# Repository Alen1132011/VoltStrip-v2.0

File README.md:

# Voltstrip V2.0

A casual, open-source 4-key mechanical macropad featuring an OLED display, a rotary encoder, and clean RGB underglow. Powered by the Seeed Studio XIAO RP2040 and running on QMK/Vial firmware so you can remap everything on the fly without breaking a sweat.

Built and submitted as part of the Hack Club Stardance program.

---

## What's Under the Hood?

* **The Controller:** Seeed Studio XIAO RP2040—super compact, fast, and budget-friendly.
* **The Keys:** 4 mechanical switches (Cherry MX compatible), meaning you can swap in whatever linears, tactiles, or clickies you prefer.
* **The Dial:** 1x EC11 rotary encoder with a built-in push button, ideal for adjusting volume, scrolling timelines, or brush sizing.
* **The Screen:** A crisp 0.91" I2C OLED display (128x32 resolution) to show off active layers, custom graphics, or profile states.
* **The Glow:** 1x addressable WS2812B RGB LED tucked underneath to give your desk that perfect ambient underglow.
* **The Software:** Fully compatible with QMK and Vial for painless, real-time layout configurations.

---

## Design & Gallery

Here is the complete project breakdown, moving from the initial electrical routing up to the final 3D-printed enclosure.

Spin it in 3D!
>  **[CLICK HERE TO VIEW THE PCB IN YOUR BROWSER via KiCanvas](https://kicanvas.org/?repo=https%3A%2F%2Fgithub.com%2FAlen1132011%2FVoltStrip-v2.0%2Ftree%2Fmain%2FPCB)**

### Layout & Concept
The overall alignment of the keys, encoder, and display panel on the top plate.

### Schematic Diagram
A clean, straightforward schematic showing how all components route back to the XIAO's GPIO pins.

### PCB Layout
Double-sided PCB design with optimized traces, dedicated ground planes, and custom silkscreen art on the back.

### Enclosure & Fit
The custom-designed 3D-printed shell. Tolerances are dialed in to ensure a perfectly flush fit for both the top plate and bottom shell pieces.

---

## Bill of Materials (BOM)

| Component | Qty | Description | Notes |
| :--- | :---: | :--- | :--- |
| **Seeed Studio XIAO RP2040** | 1 | Microcontroller Board | SMT Module / Direct Solder |
| **Cherry MX Compatible Switches** | 4 | Mechanical Key Switches | 3-pin or 5-pin plate mount |
| **EC11 Rotary Encoder** | 1 | Navigation & Volume Control | Through-Hole (THT) with push button |
| **0.91" OLED Display** | 1 | 128x32 I2C Screen | Connects via 4-pin header |
| **1N4148 Diode** | 4 | Matrix Diodes | DO-35 THT or equivalent SMD |
| **WS2812B RGB LED** | 1 | Addressable Underglow LED | 5050 / PLCC-4 package |
| **Custom Case** | 1 | 3D Printed Top & Bottom Shell | PLA or PETG (printed at 0.20mm) |

---

## Hardware Configuration & Pin Map

If you're modifying the code or setting up your own layout config, here is exactly where everything plugs into the RP2040:

* **Rows:** `GP29` (D3), `GP28` (D2)
* **Columns:** `GP27` (D1), `GP26` (D0), `GP4` (D9)
* **Rotary Encoder:** `GP2` (D8), `GP1` (D7)
* **RGB Data:** `GP3` (D10)
* **I2C Display (OLED):** Standard RP2040 SDA & SCL pins

---

## License

This project is fully open-source. Feel free to grab the files, remix the layout, spin up your own PCBs, or tweak the shell to make it your own!

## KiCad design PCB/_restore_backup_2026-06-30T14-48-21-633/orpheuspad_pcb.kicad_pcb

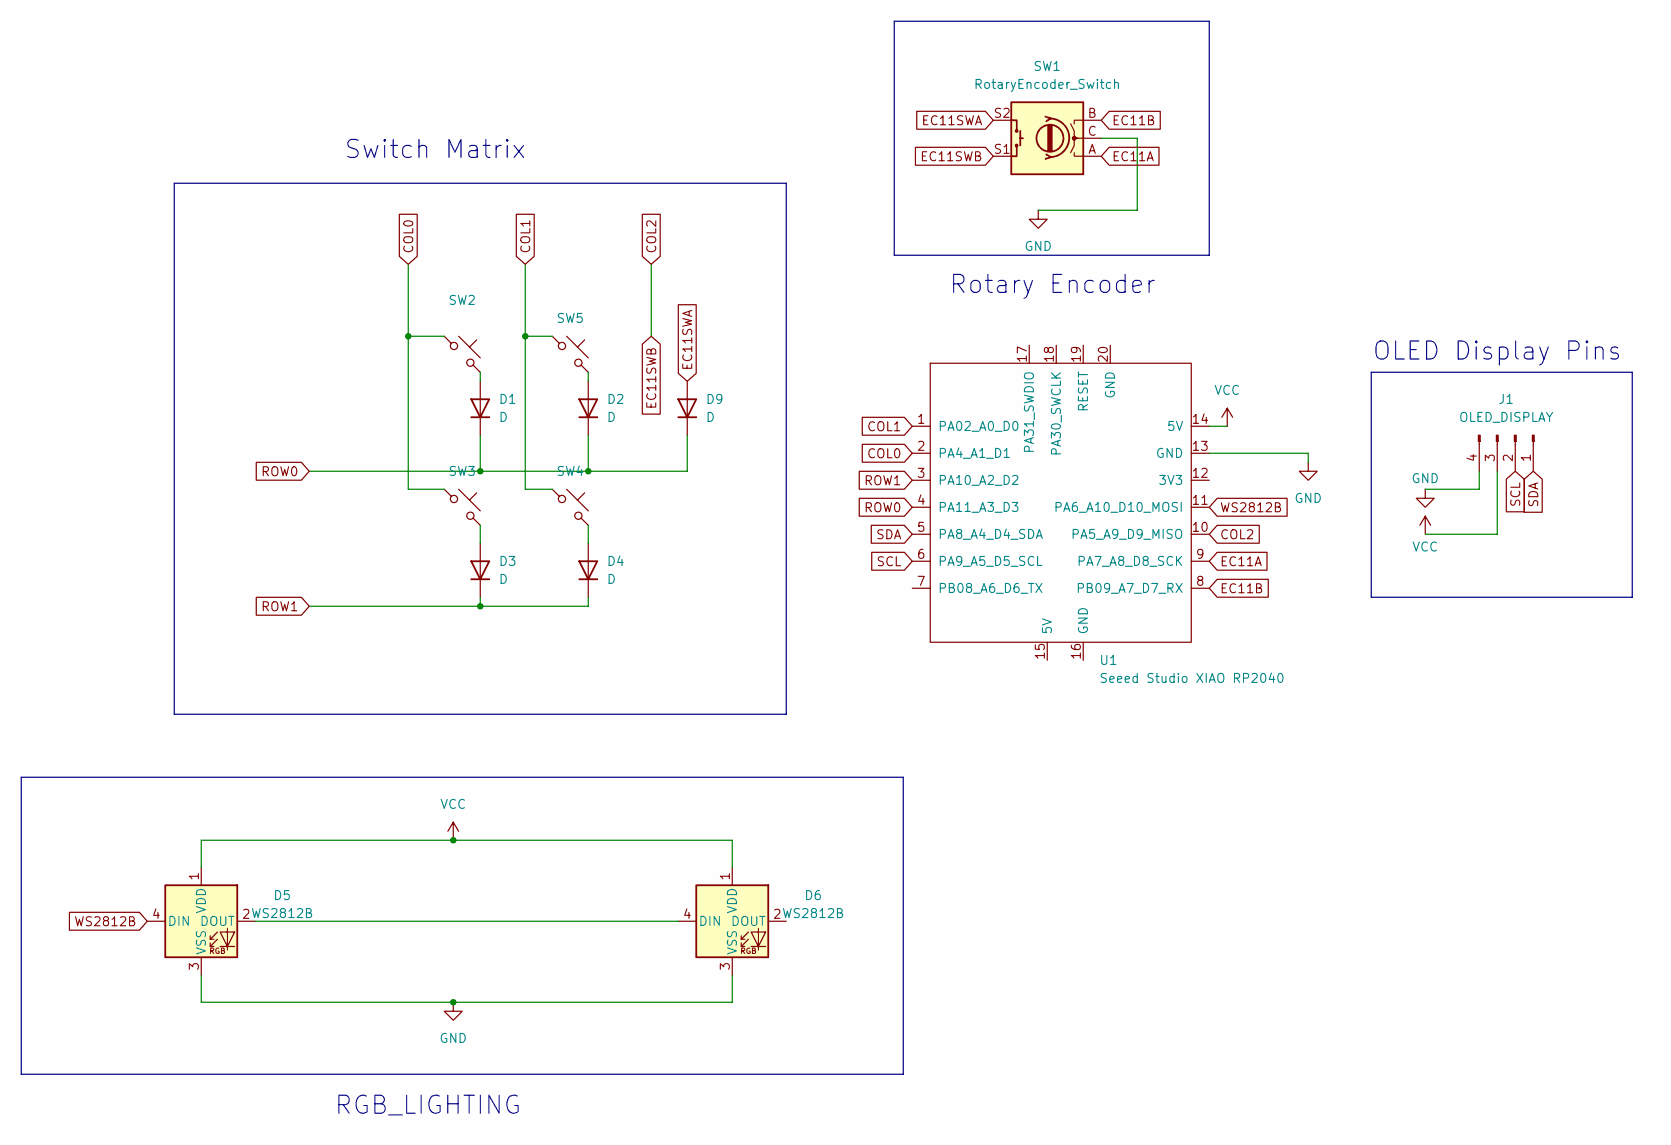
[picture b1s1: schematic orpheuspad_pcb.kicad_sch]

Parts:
D1, D2, D3, D4, D9: D; D_DO-35_SOD27_P7.62mm_Horizontal
D5, D6: WS2812B; LED_WS2812B_PLCC4_5.0x5.0mm_P3.2mm
J1: OLED_DISPLAY; PinHeader_1x04_P2.54mm_Vertical
SW1: RotaryEncoder_Switch; RotaryEncoder_Alps_EC11E-Switch_Vertical_H20mm
SW2, SW3, SW4, SW5: SW_Push_45deg; SW_Cherry_MX_1.00u_PCB
U1: Seeed Studio XIAO RP2040; XIAO-Generic-Hybrid-14P-2.54-21X17.8MM

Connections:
COL0: SW2.1, SW3.1, U1.2 (PA4_A1_D1)
COL1: SW4.1, SW5.1, U1.1 (PA02_A0_D0)
COL2: SW1.S1, U1.10 (PA5_A9_D9_MISO)
EC11A: SW1.A, U1.9 (PA7_A8_D8_SCK)
EC11B: SW1.B, U1.8 (PB09_A7_D7_RX)
EC11SWA: D9.2 (A), SW1.S2
GND: D5.3 (VSS), D6.3 (VSS), J1.4, SW1.C, U1.13 (GND)
unnamed: D1.2 (A), SW2.2
unnamed: D2.2 (A), SW5.2
unnamed: D3.2 (A), SW3.2
unnamed: D4.2 (A), SW4.2
unnamed: D5.2 (DOUT), D6.4 (DIN)
ROW0: D1.1 (K), D2.1 (K), D9.1 (K), U1.4 (PA11_A3_D3)
ROW1: D3.1 (K), D4.1 (K), U1.3 (PA10_A2_D2)
SCL: J1.2, U1.6 (PA9_A5_D5_SCL)
SDA: J1.1, U1.5 (PA8_A4_D4_SDA)
VCC: D5.1 (VDD), D6.1 (VDD), J1.3, U1.14 (5V)
WS2812B: D5.4 (DIN), U1.11 (PA6_A10_D10_MOSI)

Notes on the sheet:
RGB_LIGHTING
Switch Matrix
Rotary Encoder
OLED Display Pins

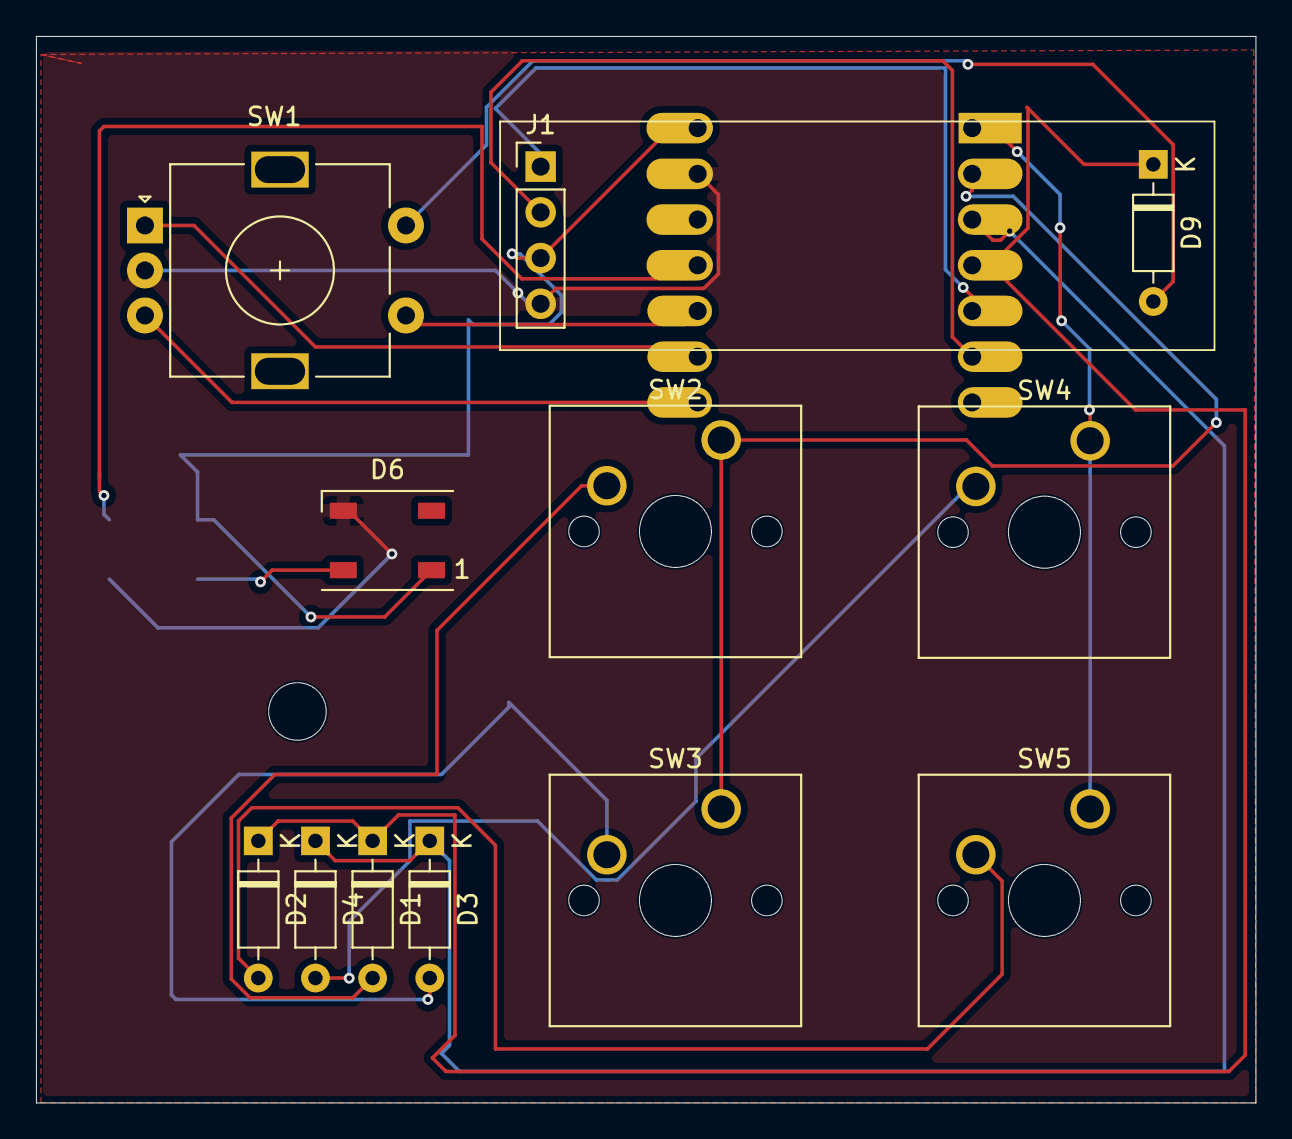
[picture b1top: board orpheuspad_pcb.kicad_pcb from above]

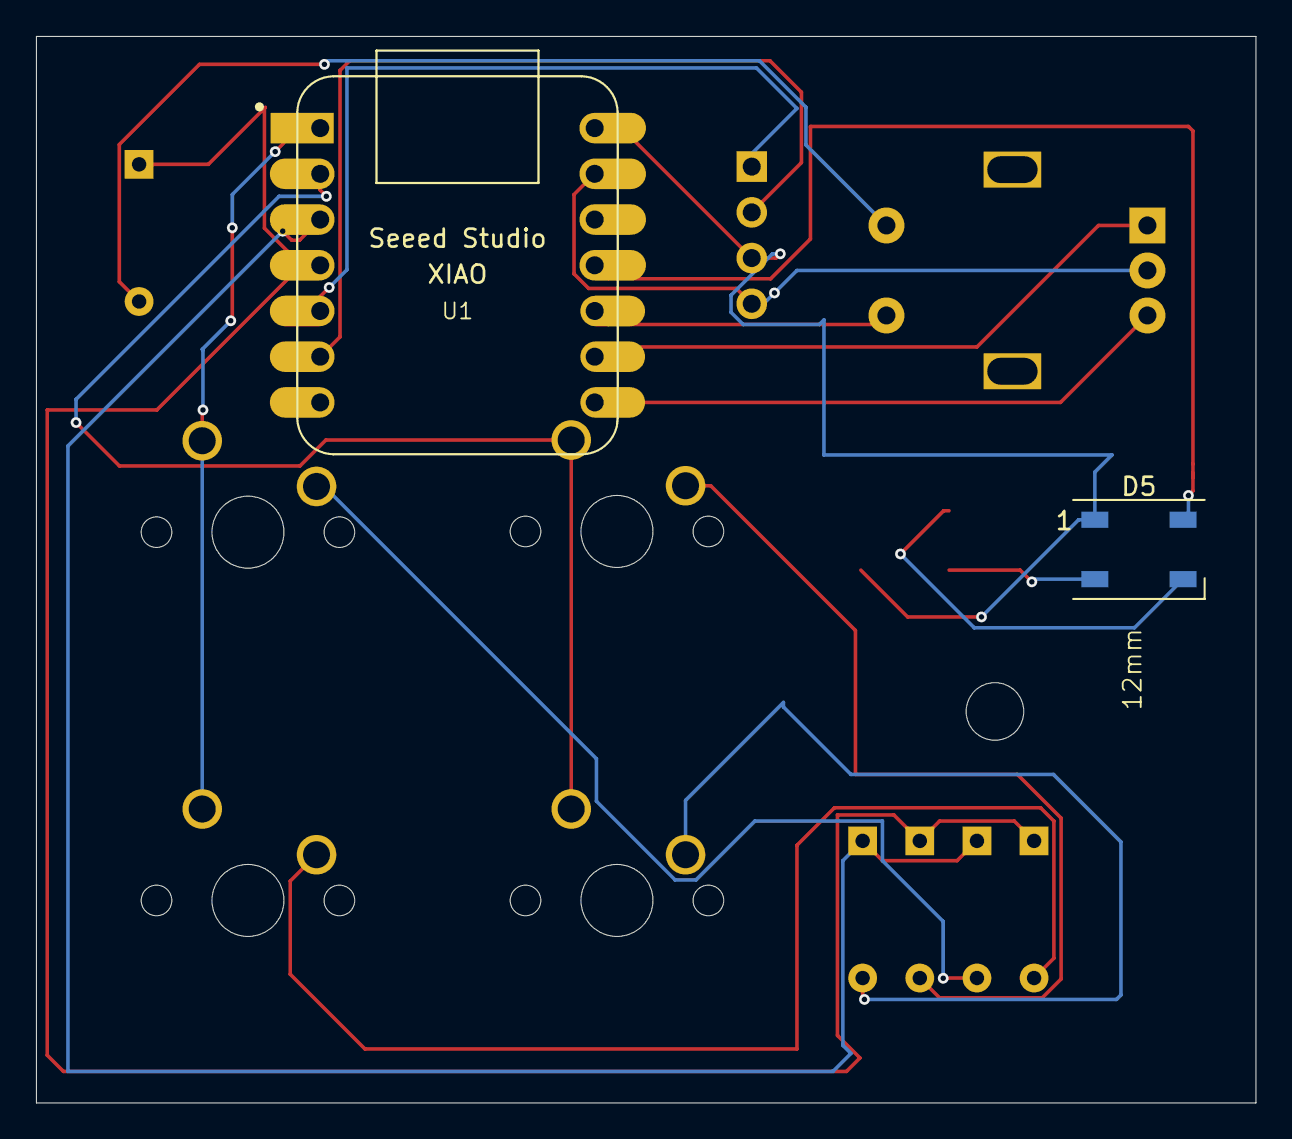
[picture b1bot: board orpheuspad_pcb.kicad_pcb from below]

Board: 2 copper layers, 67.8 x 59.2 mm, 14 parts (2 on the bottom side), 18 nets.
